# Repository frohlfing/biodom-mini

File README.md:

# Projekt "Biodom Mini" – Ein Hightech-Gewächshaus

Das Ziel ist ein Mini-Gewächshaus für anspruchsvolle Pflanzen, das automatisch für ein tropisches Klima sorgt.

**Features:**

- Künstliche Sonne
- Konstante Temperatur
- Konstante Luftfeuchtigkeit
- Automatische Bewässerung
- Kamera (schießt regelmäßig Bilder für Zeitraffer-Video)
- Display (zeigt aktuelle Werte an)
- Webinterface (über WLAN erreichbar)

## Projektdokumentation

Eine detailliertere technische Dokumentation befindet sich in [Projektdokumentation.md](docs/Projektdokumentation.md).

## Lizenz

Dieses Projekt steht unter der [GPL-3.0-Lizenz](LICENSE).

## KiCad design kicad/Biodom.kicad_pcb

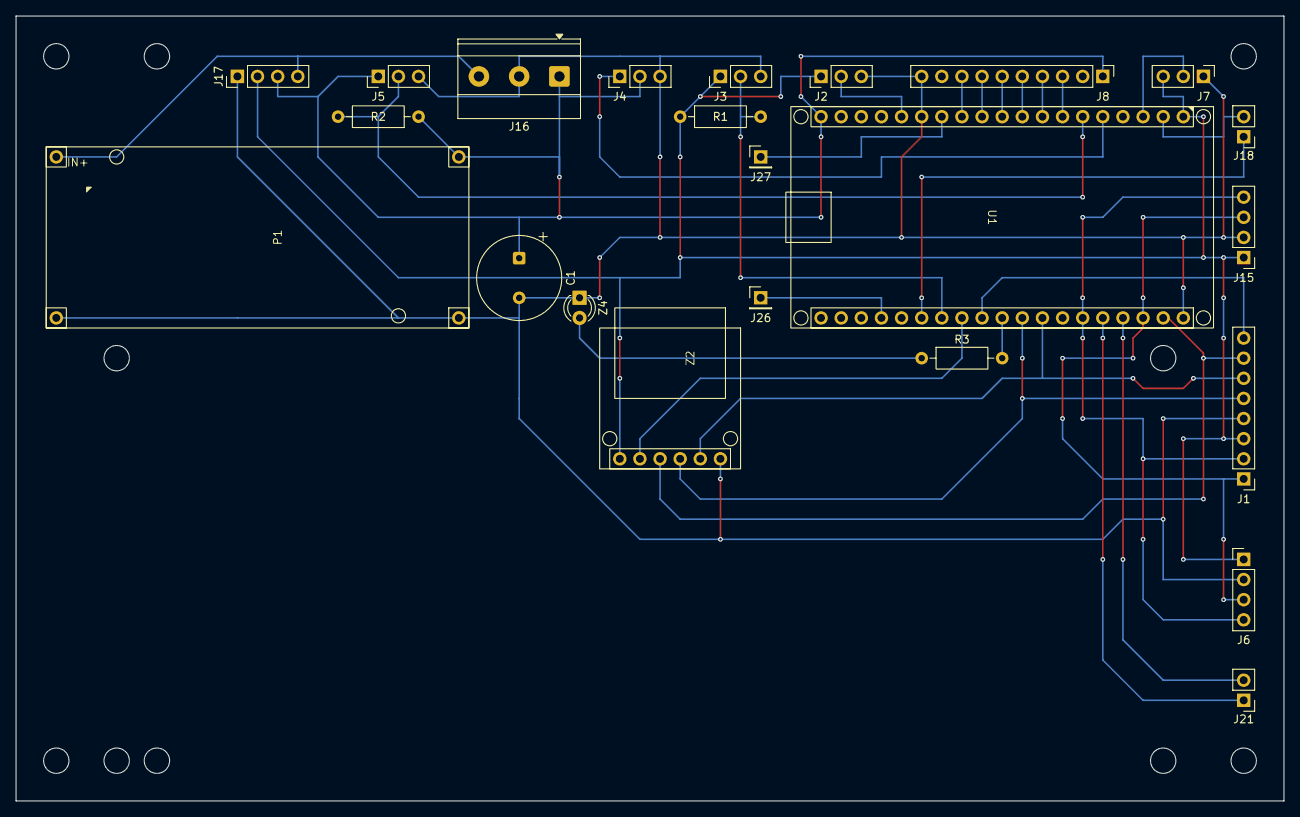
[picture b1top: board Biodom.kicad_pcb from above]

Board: 2 copper layers, 160.0 x 99.1 mm, 23 parts (0 on the bottom side), 30 nets.

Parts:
C1: 470µF; CP_Radial_Tantal_D10.5mm_P5.00mm
J1: Kamera; PinHeader_1x08_P2.54mm_Vertical
J2: Luft; PinHeader_1x03_P2.54mm_Vertical
J3: Bodentemperatur; PinHeader_1x03_P2.54mm_Vertical
J4: Bodenfeuchte; PinHeader_1x03_P2.54mm_Vertical
J5: Wasserstand; PinHeader_1x03_P2.54mm_Vertical
J6: Lichtstärke; PinHeader_1x04_P2.54mm_Vertical
J7: Reserve S6; PinHeader_1x03_P2.54mm_Vertical
J8: Relais; PinHeader_1x10_P2.54mm_Vertical
J15: Display; PinHeader_1x04_P2.54mm_Vertical
J16: DC; TerminalBlock_Phoenix_MKDS-1,5-3-5.08_1x03_P5.08mm_Horizont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
J17: PWR; PinHeader_1x04_P2.54mm_Vertical
J18: RST; PinHeader_1x02_P2.54mm_Vertical
J21: UART; PinHeader_1x02_P2.54mm_Vertical
J26: TDO; PinHeader_1x01_P2.54mm_Vertical
J27: TDI; PinHeader_1x01_P2.54mm_Vertical
P1: Spannungsteiler; XL4015_Module_Socket
R1: 4,7kΩ; R_Axial_DIN0207_L6.3mm_D2.5mm_P10.16mm_Horizontal
R2: 10kΩ; R_Axial_DIN0207_L6.3mm_D2.5mm_P10.16mm_Horizontal
R3: 330Ω; R_Axial_DIN0207_L6.3mm_D2.5mm_P10.16mm_Horizontal
U1: ESP32; ESP32_DevKitC_V2_Socket
Z2: SD-Karte; MicroSD_SPI_Modul_Socket
Z4: LED; LED_D3.0mm

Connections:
+3V3: J1.3, J2.1, J3.1, J6.1, J7.3, J15.1, J17.2, R1.1, U1.1 (3V3), Z2.1 (3.3V)
+5V: C1.1, J4.2, J5.1, J8.1, J16.1, J17.3, P1.3 (OUT+), R2.1, U1.19 (5V)
+12V: J16.3, J17.4, P1.1 (IN+)
/EN: J18.2, U1.2 (EN)
/G0: J18.1, U1.25 (G0)
/G1: J21.2, U1.35 (TXD)
/G3: J21.1, U1.34 (RXD)
/G4: J3.2, R1.2, U1.26 (G4)
/G5: R3.2, U1.29 (G5)
/G12: J27.1, U1.13 (G12)
/G13: J2.2, U1.15 (G13)
/G14: J8.8, U1.12 (G14)
/G15: J26.1, U1.23 (G15)
/G16: U1.27 (G16), Z2.2 (CS)
/G17: J1.8, U1.28 (G17)
/G18: J1.5, U1.30 (G18), Z2.4 (CLK)
/G19: J1.6, U1.31 (G19), Z2.5 (MISO)
/G21: J1.2, J6.4, J15.4, U1.33 (G21)
/G22: J1.1, J6.3, J15.3, U1.36 (G22)
/G23: J1.7, U1.37 (G23), Z2.3 (MOSI)
/G25: J8.5, U1.9 (G25)
/G26: J8.6, U1.10 (G26)
/G27: J8.7, U1.11 (G27)
/G32: J8.3, U1.7 (G32)
/G33: J8.4, U1.8 (G33)
/G34: J4.1, U1.5 (G34)
/G35: J5.2, R2.2, U1.6 (G35)
/G36: J7.2, U1.3 (SP)
/LED+: R3.1, Z4.2 (A)
GND: C1.2, J1.4, J2.3, J3.3, J4.3, J5.3, J6.2, J7.1, J8.10, J15.2, J16.2, J17.1, P1.2 (IN-), P1.4 (OUT-), U1.14 (GND), U1.38 (GND), Z2.6 (GND), Z4.1 (K)

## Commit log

2025-11-01 .gitignore is now working
2025-11-03 AM2302 und DS18B20 Sensoren initial implementiert
2025-11-04 für jedes Bauteile eine lokale Lib hinzugefügt
2025-11-11 Einrückung korrigiert
2025-11-11 typos
2025-11-19 Sketches ausgelagert
2025-11-25 ConfigManager
2025-11-25 SettingsManager
2025-11-25 Ausbau Webinterface
2025-11-28 READMEs überarbeitet
2025-11-29 WebInterface in WebUI umbenannt
2025-12-06 ArduCAM-Lib überarbeitet
2025-12-07 Frontend für Bilder erweitert
2025-12-09 bugfix
2025-12-10 Kräftig aufgeräumt!
2025-12-11 Release 1
